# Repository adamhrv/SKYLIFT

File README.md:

# SkyLift

SkyLift is an experimental Wi-Fi/BT geolocation spoofing device that uses the ESP8266 or ESP32 boards to broadcast Wi-Fi beacon frames or BT advertisements that emulate the wireless infrastructure from a remote/target location. The above example shows a successful georelocation to Peter Thiel's vacation house in Hawaii from the [DataPools](https://ahprojects.com/datapools) project (2018).

Mobile devices (i.e. iOS and Android) rely on this information for core geolocation services when space-based GPS signals are weak, which often occurs in urban areas or basement-like spaces.

The project has been most successful when using multiple SkyLift devices in outdoor settings positioned similar to the real (target) routers, overwhelming the existing Wi-Fi infrastructure and confusing most mobile devices. It also worked well in crowded indoor environments where bodies (which are 2/3 water) absorb Wi-Fi energy because 2.4GHz is the resonant frequency of water molecules.

However, it's still unclear what the best settings are for the Wi-Fi packet structure, what other factors affect ability to override core geolocation services, and if mobile operating systems have integrated anti-spoofing technologies. Most likely success with this code will be limited in general settings, though the low cost of prototyping hardware and potentially significant results make it a worthwhile project to explore further.

## Setup Arduino IDE

- Download Arduino IDE
- Install boards in File > Preferences: Additional boards manager URLs
- board URLs `http://arduino.esp8266.com/stable/package_esp8266com_index.json,https://raw.githubusercontent.com/espressif/arduino-esp32/gh-pages/package_esp32_index.json`
- Select board:
	- NodeMCU ESP32 is "ESP32 Dev Module"
- Set upload speed in Tools > Upload Speed to maximum 460800

## Setup Python

Tested for Linux Ubuntu 20.04

Python	
```
python -m venv venv
source venv/bin/activate
python setup.py develop
skylift
```

```
Usage: skylift [OPTIONS] COMMAND [ARGS]...

  SkyLift

Options:
  --help  Show this message and exit.

Commands:
  convert-scan   Convert WiFi/BT network can to Networks JSON
  create-sketch  Creates new Arduino sketch from template
  ```

## Usage

Convert WiFi/BT scan to networks JSON
```python
skylift convert-scan -i path/to/scan.csv -o path/to/scan.json
```

Create Arduino sketch from template
```python
skylift create-sketch	-i path/to/scan.json -o path/to/scan-arduino/
```

Customize more parameters
```python
skylift create-sketch
	-i path/to/scan.json
	-o path/to/scan-arduino/
	--max-networks 12
	--board esp32
```

## Troubleshooting

Linux
- Ensure USB serial is allowed `sudo chmod a+rw /dev/ttyUSB0`
- Ensure pyserial is installed `pip install pyserial --user`

## TODO
- [ ] add BLE adverts
- [ ] review and confirm WiFi packet structure
- [ ] add randomness to WiFi packets
- [ ] add Wigle API
- [ ] add emoji SSID support 🙃

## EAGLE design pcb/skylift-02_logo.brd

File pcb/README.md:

# Skylift PCB

Board and schematic for building a Wi-Fi Geolocation Spoofing device

### Eagle Files

- SkyLift Eagle PCB board:`skylift-02_logo.brd`
- SkyLift Eagle PCB schematic:`skylift-02_logo.sch`

### BOM

| Part | Component  | Quantity  |
|---|---|---|
| U1 | ESP8266 NodeMCU 12-E | 1 |
| S1,S2,S3 | WS-TASU SMT Tact Switch with Boss Design 4.7x3.5mm | 3 |
| U2 | 0.96" OLED | 1 |
| J1 | solder jumper | - |

### Order sources

- push button switch: <https://katalog.we-online.de/en/em/TASU_3_5X4_7_SMD_SIDE_PUSH_BOSS_DESIGN>
- ESP8266 NodeMCU 12 or 12E
	- [eBay](http://www.ebay.com/itm/NodeMcu-Lua-WIFI-Internet-Things-development-board-based-ESP8266-CP2102-module-/201542946669?hash=item2eece54f6d:g:EOIAAOSw4q9XT5mo) (cheaper)
	- [Amazon.com](https://www.amazon.com/HiLetgo-Version-NodeMCU-Internet-Development/dp/B010O1G1ES/) (quicker)

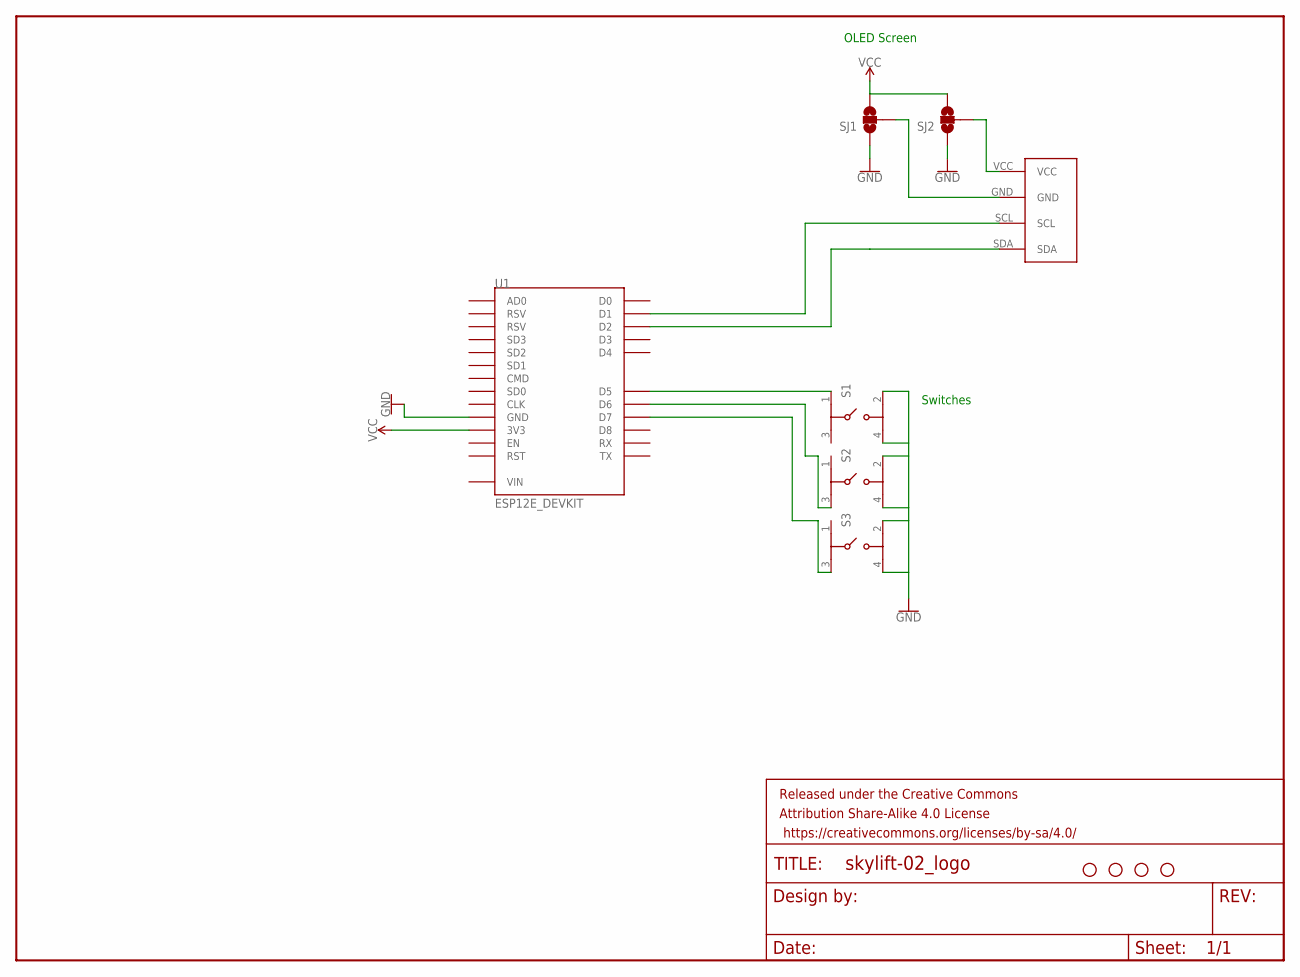
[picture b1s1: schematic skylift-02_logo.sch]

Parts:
FRAME1: FRAME-LETTERNO_PACKAGE; DUMMY
H1, H2, H3, H4: STAND-OFFTIGHT; STAND-OFF-TIGHT
S1, S2, S3: 436333045822
SJ1, SJ2: SOLDERJUMPER_2WAY-OLDT; SJ_2
U1: ESP12E_DEVKIT
U2: I2C_OLED; I2C_OLED_PACKAGE

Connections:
D5: S1.1 (3), U1.D5
D6: S2.3 (1), U1.D6
D7: S3.3 (1), U1.D7
GND: S1.2 (4), S1.4 (2), S2.2 (4), S2.4 (2), S3.2 (4), S3.4 (2), SJ1.1, SJ2.1, U1.GND@0 (GND), U1.GND@1 (GND), U1.GND@2 (GND), U1.GND@3 (GND)
unnamed: SJ1.2, U2.GND
unnamed: SJ2.2, U2.VCC
SCL: U1.D1, U2.SCL
SDA: U1.D2, U2.SDA
VCC: SJ1.3, SJ2.3, U1.3V3@0 (3V3), U1.3V3@1 (3V3), U1.3V3@2 (3V3)
VIN: U1.VIN

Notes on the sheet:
Switches
OLED Screen

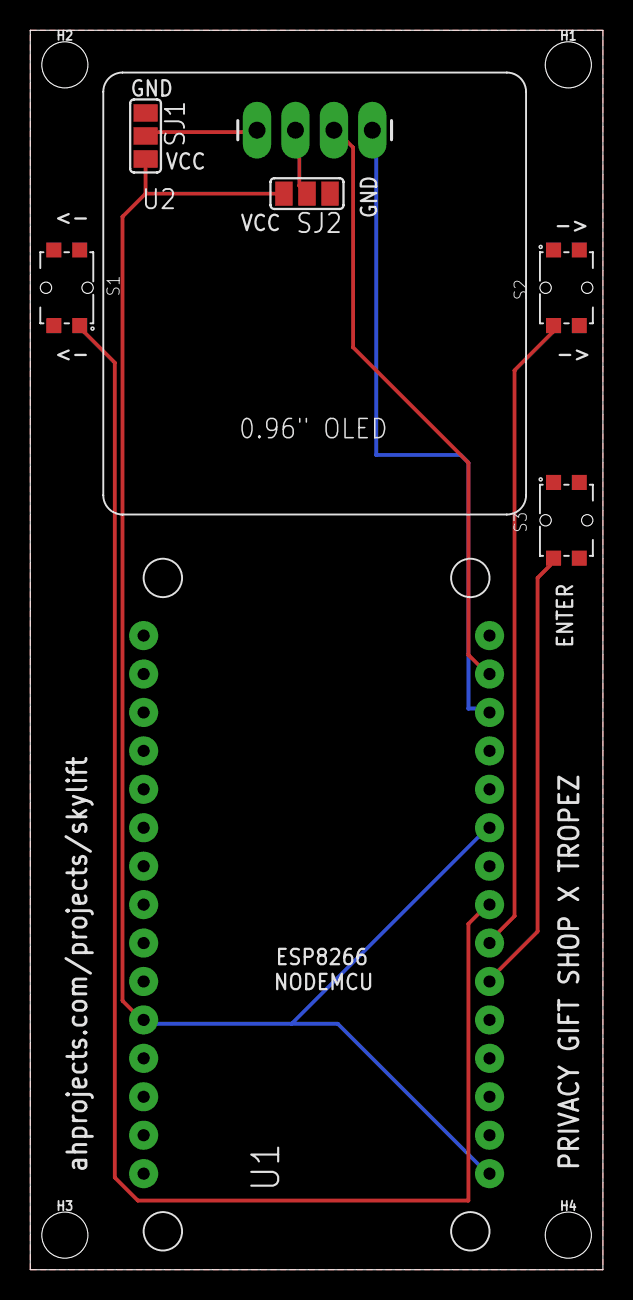
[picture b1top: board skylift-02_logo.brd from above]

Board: 2 copper layers, 37.8 x 81.9 mm, 12 parts (0 on the bottom side), 9 nets.

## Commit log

2017-05-05 updating txt
2017-05-05 added ebay link
2017-05-06 udpated text
2017-05-13 added scan from John Kiriakou Disruption Lab keynote
2017-09-28 Create LICENSE
2018-05-17 fix: python3 compatibility problem add error handling to wigle_to_json.py
2018-05-17 v4 notes
2019-01-29 remove v1
2019-01-29 add tmp docs
2019-01-29 add tmp app
2019-01-29 keeps
2019-01-29 remove vendor names
2019-01-29 reset
2019-01-29 add zuck demo
2019-01-29 add example arudino sketch
2019-01-29 add demo from cryptorave BCN
2019-01-31 add wigle export parser
2019-01-31 add prelim PCB
2019-02-01 add old v0.5 files
2019-02-01 tmp update
2019-02-04 add demo sketch and tests
2019-02-04 add demo data for Menlo Park
2019-02-04 update docs, in progress
2019-02-04 update net parser
2019-02-04 update docs
2019-02-10 update readme, wifi deafult ON
2019-02-21 update BoM
2019-04-24 upgrade urllib3>=1.24.2
2019-06-25 fix csv parse err, prevent write on err
2019-06-25 update pip libs
2019-06-26 ios example
2019-06-26 fix ios
2020-04-10 add TODO
2020-07-29 Update cli_jobs.py
    Fix an typo error in line 102.
2021-03-27 Update cli_jobs.py
    Fix missing dot preventing compile
2021-03-27 Update geo_utils.py
    Update function call to geodesic instead of deprecated vincenty
    See: https://geopy.readthedocs.io/en/stable/changelog_2xx.html#breaking-changes
2021-04-30 Bump urllib3 from 1.25.3 to 1.25.8
    Bumps [urllib3](https://github.com/urllib3/urllib3) from 1.25.3 to 1.25.8.
    - [Release notes](https://github.com/urllib3/urllib3/releases)
    - [Changelog](https://github.com/urllib3/urllib3/blob/main/CHANGES.rst)
    - [Commits](https://github.com/urllib3/urllib3/compare/1.25.3...1.25.8)
2022-10-07 Rebuild simplified
2022-10-07 Bump numpy from 1.16.0 to 1.22.0 in /archive
    Bumps [numpy](https://github.com/numpy/numpy) from 1.16.0 to 1.22.0.
    - [Release notes](https://github.com/numpy/numpy/releases)
    - [Changelog](https://github.com/numpy/numpy/blob/main/doc/RELEASE_WALKTHROUGH.rst)
    - [Commits](https://github.com/numpy/numpy/compare/v1.16.0...v1.22.0)
    ---
    updated-dependencies:
2022-10-07 Bump urllib3 from 1.25.3 to 1.26.5 in /archive
    Bumps [urllib3](https://github.com/urllib3/urllib3) from 1.25.3 to 1.26.5.
    - [Release notes](https://github.com/urllib3/urllib3/releases)
    - [Changelog](https://github.com/urllib3/urllib3/blob/main/CHANGES.rst)
    - [Commits](https://github.com/urllib3/urllib3/compare/1.25.3...1.26.5)
    ---
    updated-dependencies:
2022-10-07 Bump urllib3 from 1.25.3 to 1.26.5
    Bumps [urllib3](https://github.com/urllib3/urllib3) from 1.25.3 to 1.26.5.
    - [Release notes](https://github.com/urllib3/urllib3/releases)
    - [Changelog](https://github.com/urllib3/urllib3/blob/main/CHANGES.rst)
    - [Commits](https://github.com/urllib3/urllib3/compare/1.25.3...1.26.5)
    ---
    updated-dependencies:
2022-10-07 Bump numpy from 1.16.0 to 1.22.0
    Bumps [numpy](https://github.com/numpy/numpy) from 1.16.0 to 1.22.0.
    - [Release notes](https://github.com/numpy/numpy/releases)
    - [Changelog](https://github.com/numpy/numpy/blob/main/doc/HOWTO_RELEASE.rst)
    - [Commits](https://github.com/numpy/numpy/compare/v1.16.0...v1.22.0)
    ---
    updated-dependencies:
2022-10-12 setup as cli alias
2022-10-12 mv to src, use setup for install
2022-10-12 rm due to outdated deps
2022-10-12 fix typo
2022-10-13 fix path parent
2022-10-13 use memcpy, preset ssid lengths
2022-10-13 tidy
2022-10-13 Replace main image
2023-03-27 clean
2023-03-27 --board
2023-03-27 drop dupes wigle
2024-04-25 Bump pydantic from 1.10.2 to 1.10.13
    Bumps [pydantic](https://github.com/pydantic/pydantic) from 1.10.2 to 1.10.13.
    - [Release notes](https://github.com/pydantic/pydantic/releases)
    - [Changelog](https://github.com/pydantic/pydantic/blob/main/HISTORY.md)
    - [Commits](https://github.com/pydantic/pydantic/compare/v1.10.2...v1.10.13)
    ---
    updated-dependencies:
2025-01-11 Make reading network data more tolerant of input json file format
    Adopt changes from skylift-internal fork by thel3l

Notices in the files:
parts and their libraries:
SparkFun-Aesthetics: Licensing: Creative Commons ShareAlike 4.0 International - https://creativecommons.org/licenses/by-sa/4.0
Eagle_SWITCHES: Copyright: Würth Elektronik
SparkFun-Aesthetics: Released under the Creative Commons Attribution Share-Alike 4.0 License
